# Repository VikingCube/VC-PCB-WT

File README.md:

# VikingCube WT PCB

Repository for VikingCube WT Boards

https://vikingcube.com

# Legal
You are free to download, build, modify VikingCube Midi with absolutely no fee and any kind of guarantee. We believe in the mindset of opensource - if you like please
mark the source with references for this repositroy or our website: www.vikingcube.com

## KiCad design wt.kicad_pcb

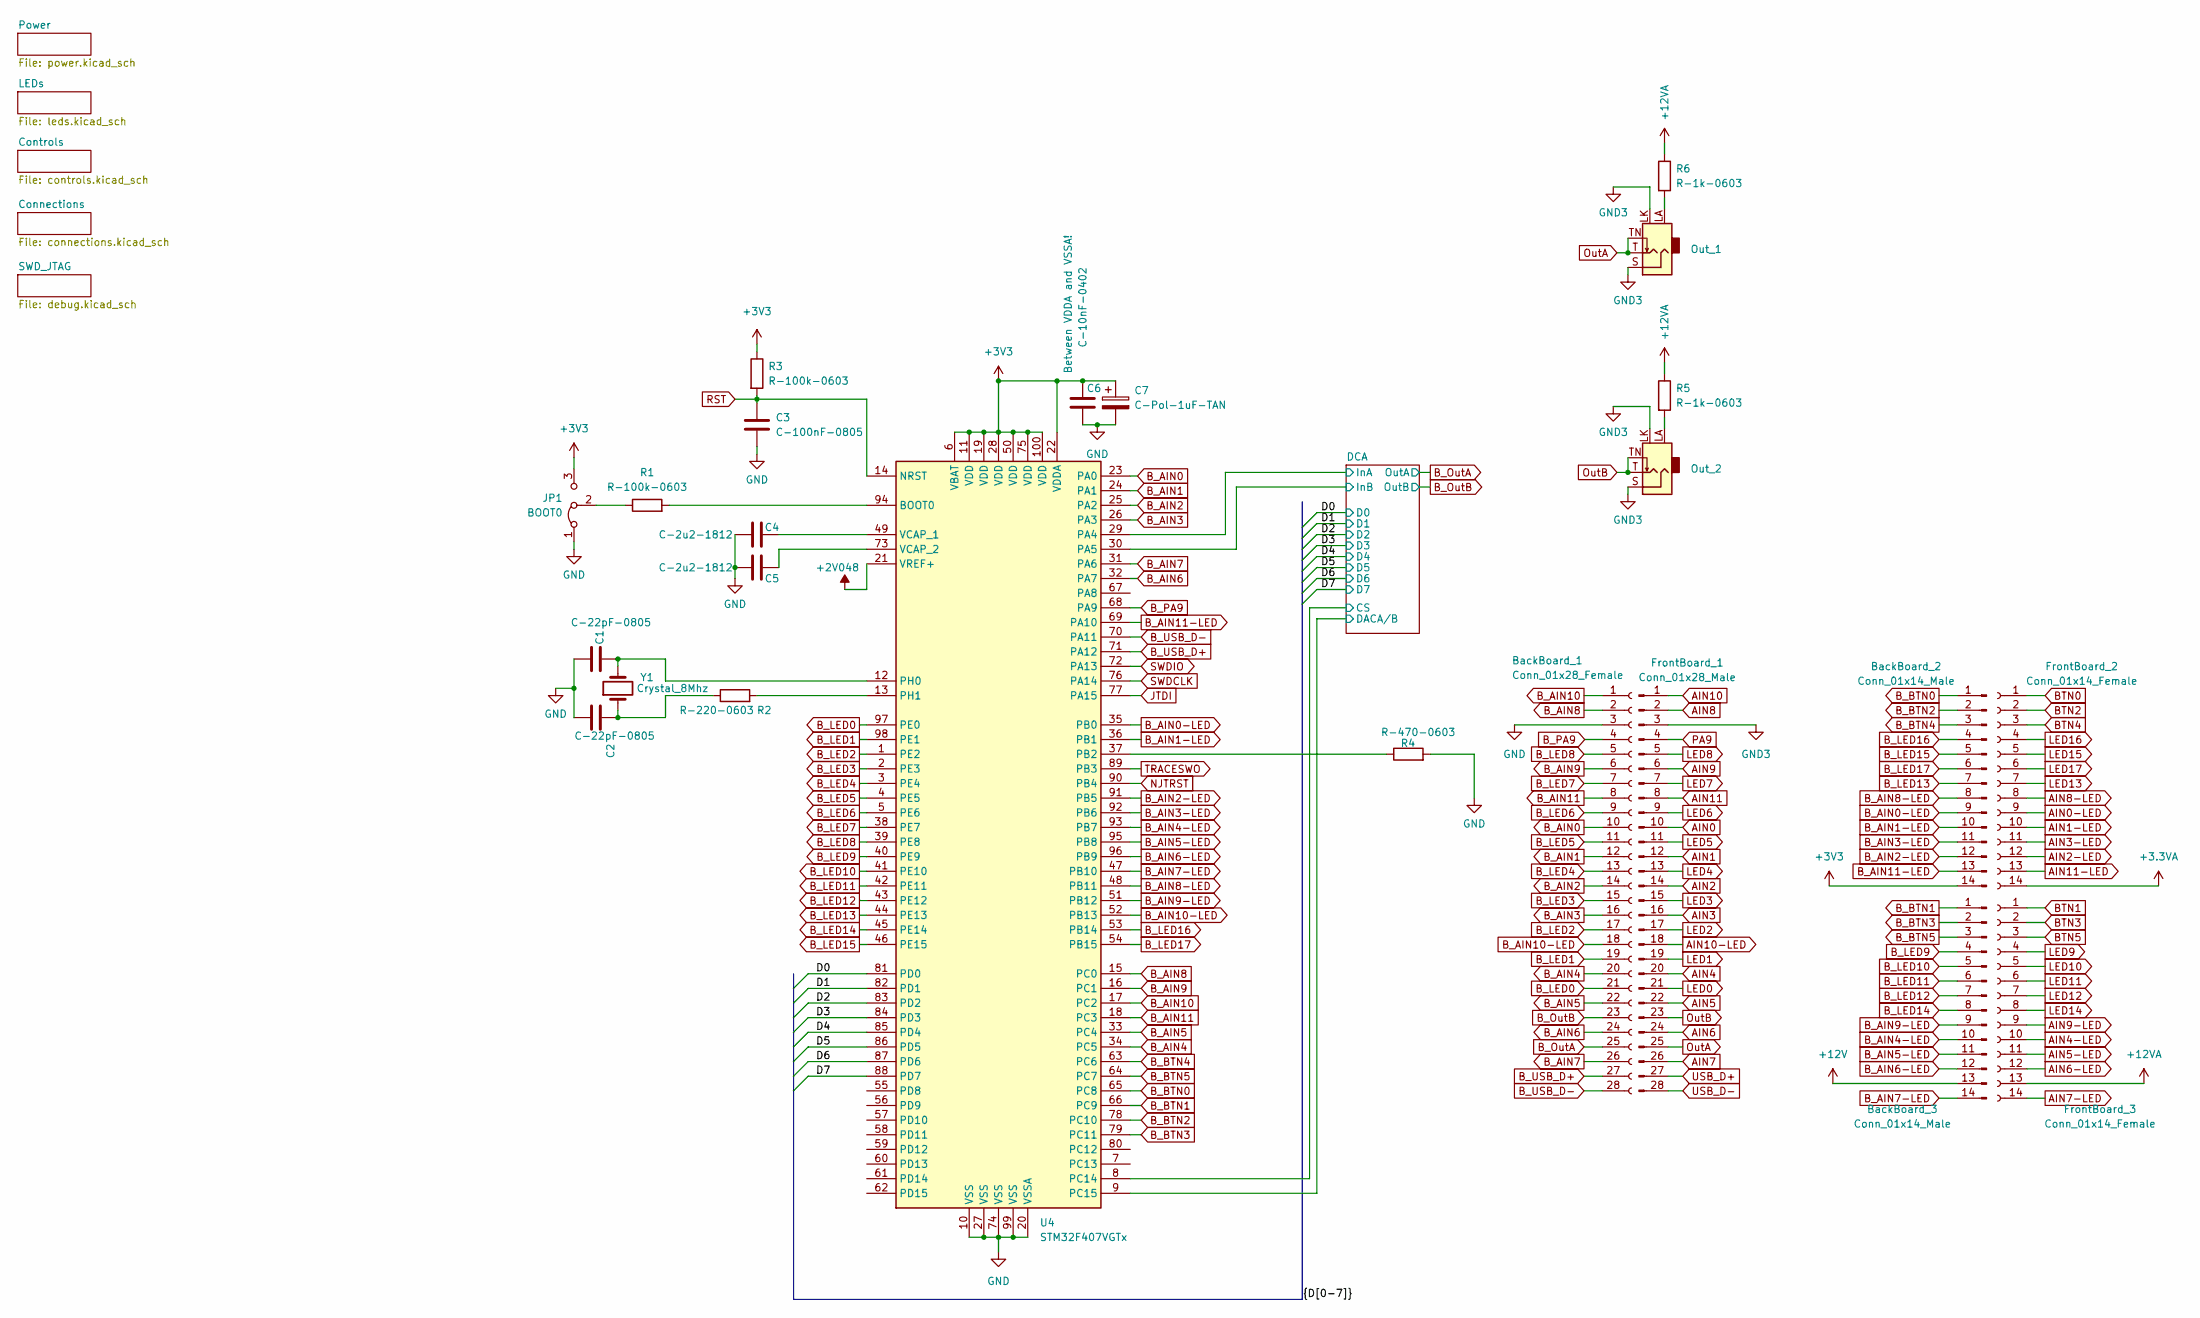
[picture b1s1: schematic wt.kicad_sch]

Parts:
BackBoard_1: Conn_01x28_Female; PinSocket_2x14_P2.54mm_Vertical
BackBoard_2, BackBoard_3: Conn_01x14_Male; PinHeader_1x14_P2.54mm_Vertical
C1, C2: C-22pF-0805; C_0805_2012Metric_Pad1.18x1.45mm_HandSolder; Tolerance 5%; Voltage 50V
C3: C-100nF-0805; C_0805_2012Metric_Pad1.18x1.45mm_HandSolder
C4, C5: C-2u2-1812; C_0603_1608Metric
C6: C-10nF-0402; C_0402_1005Metric
C7: C-Pol-1uF-TAN; CP_EIA-3216-18_Kemet-A
FrontBoard_1: Conn_01x28_Male; PinHeader_2x14_P2.54mm_Vertical
FrontBoard_2, FrontBoard_3: Conn_01x14_Female; PinSocket_1x14_P2.54mm_Vertical
JP1: BOOT0; PinHeader_1x03_P2.54mm_Vertical
Out_1, Out_2: LUM-1502-03_3.5mm_mono_vertical_jack; LUM 1502-03 LED
R1, R3: R-100k-0603; R_0603_1608Metric
R2: R-220-0603; R_0201_0603Metric_Pad0.64x0.40mm_HandSolder
R4: R-470-0603; R_0201_0603Metric_Pad0.64x0.40mm_HandSolder; Tolerance 5%
R5, R6: R-1k-0603; R_0603_1608Metric_Pad0.98x0.95mm_HandSolder; Tolerance 5%
U4: STM32F407VGTx; LQFP-100_14x14mm_P0.5mm
Y1: Crystal_8Mhz; HC49-4HSMX

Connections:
1V25: U4.21 (VREF+); also elsewhere on the board
+3.3VA: FrontBoard_2.14; also elsewhere on the board
+3V3: BackBoard_2.14, C6.1, C7.1, JP1.3 (B), R3.1, U4.6 (VBAT), U4.11 (VDD), U4.19 (VDD), U4.22 (VDDA), U4.28 (VDD), U4.50 (VDD), U4.75 (VDD), U4.100 (VDD); also elsewhere on the board
+12V: BackBoard_3.13; also elsewhere on the board
+12VA: FrontBoard_3.13, R5.1, R6.1; also elsewhere on the board
/D0: U4.81 (PD0); also elsewhere on the board
/D1: U4.82 (PD1); also elsewhere on the board
/D2: U4.83 (PD2); also elsewhere on the board
/D3: U4.84 (PD3); also elsewhere on the board
/D4: U4.85 (PD4); also elsewhere on the board
/D5: U4.86 (PD5); also elsewhere on the board
/D6: U4.87 (PD6); also elsewhere on the board
/D7: U4.88 (PD7); also elsewhere on the board
/DCA/CS: U4.8 (PC14); also elsewhere on the board
/DCA/DACA/B: U4.9 (PC15); also elsewhere on the board
/DCA/InA: U4.29 (PA4); also elsewhere on the board
/DCA/InB: U4.30 (PA5); also elsewhere on the board
AIN0: FrontBoard_1.10; also elsewhere on the board
AIN0-LED: FrontBoard_2.9; also elsewhere on the board
AIN1: FrontBoard_1.12; also elsewhere on the board
AIN1-LED: FrontBoard_2.10; also elsewhere on the board
AIN2: FrontBoard_1.14; also elsewhere on the board
AIN2-LED: FrontBoard_2.12; also elsewhere on the board
AIN3: FrontBoard_1.16; also elsewhere on the board
AIN3-LED: FrontBoard_2.11; also elsewhere on the board
AIN4: FrontBoard_1.20; also elsewhere on the board
AIN4-LED: FrontBoard_3.10; also elsewhere on the board
AIN5: FrontBoard_1.22; also elsewhere on the board
AIN5-LED: FrontBoard_3.11; also elsewhere on the board
AIN6: FrontBoard_1.24; also elsewhere on the board
AIN6-LED: FrontBoard_3.12; also elsewhere on the board
AIN7: FrontBoard_1.26; also elsewhere on the board
AIN7-LED: FrontBoard_3.14; also elsewhere on the board
AIN8: FrontBoard_1.2; also elsewhere on the board
AIN8-LED: FrontBoard_2.8; also elsewhere on the board
AIN9: FrontBoard_1.6; also elsewhere on the board
AIN9-LED: FrontBoard_3.9; also elsewhere on the board
AIN10: FrontBoard_1.1; also elsewhere on the board
AIN10-LED: FrontBoard_1.18; also elsewhere on the board
AIN11: FrontBoard_1.8; also elsewhere on the board
AIN11-LED: FrontBoard_2.13; also elsewhere on the board
BTN0: FrontBoard_2.1; also elsewhere on the board
BTN1: FrontBoard_3.1; also elsewhere on the board
BTN2: FrontBoard_2.2; also elsewhere on the board
BTN3: FrontBoard_3.2; also elsewhere on the board
BTN4: FrontBoard_2.3; also elsewhere on the board
BTN5: FrontBoard_3.3; also elsewhere on the board
B_AIN0: BackBoard_1.10, U4.23 (PA0)
B_AIN0-LED: BackBoard_2.9, U4.35 (PB0)
B_AIN1: BackBoard_1.12, U4.24 (PA1)
B_AIN1-LED: BackBoard_2.10, U4.36 (PB1)
B_AIN2: BackBoard_1.14, U4.25 (PA2)
B_AIN2-LED: BackBoard_2.12, U4.91 (PB5)
B_AIN3: BackBoard_1.16, U4.26 (PA3)
B_AIN3-LED: BackBoard_2.11, U4.92 (PB6)
B_AIN4: BackBoard_1.20, U4.34 (PC5)
B_AIN4-LED: BackBoard_3.10, U4.93 (PB7)
B_AIN5: BackBoard_1.22, U4.33 (PC4)
B_AIN5-LED: BackBoard_3.11, U4.95 (PB8)
B_AIN6: BackBoard_1.24, U4.32 (PA7)
B_AIN6-LED: BackBoard_3.12, U4.96 (PB9)
B_AIN7: BackBoard_1.26, U4.31 (PA6)
B_AIN7-LED: BackBoard_3.14, U4.47 (PB10)
B_AIN8: BackBoard_1.2, U4.15 (PC0)
B_AIN8-LED: BackBoard_2.8, U4.48 (PB11)
B_AIN9: BackBoard_1.6, U4.16 (PC1)
B_AIN9-LED: BackBoard_3.9, U4.51 (PB12)
B_AIN10: BackBoard_1.1, U4.17 (PC2)
B_AIN10-LED: BackBoard_1.18, U4.52 (PB13)
B_AIN11: BackBoard_1.8, U4.18 (PC3)
B_AIN11-LED: BackBoard_2.13, U4.69 (PA10)
B_BTN0: BackBoard_2.1, U4.65 (PC8)
B_BTN1: BackBoard_3.1, U4.66 (PC9)
B_BTN2: BackBoard_2.2, U4.78 (PC10)
B_BTN3: BackBoard_3.2, U4.79 (PC11)
B_BTN4: BackBoard_2.3, U4.63 (PC6)
B_BTN5: BackBoard_3.3, U4.64 (PC7)
B_LED0: BackBoard_1.21, U4.97 (PE0)
B_LED1: BackBoard_1.19, U4.98 (PE1)
B_LED2: BackBoard_1.17, U4.1 (PE2)
B_LED3: BackBoard_1.15, U4.2 (PE3)
B_LED4: BackBoard_1.13, U4.3 (PE4)
B_LED5: BackBoard_1.11, U4.4 (PE5)
B_LED6: BackBoard_1.9, U4.5 (PE6)
B_LED7: BackBoard_1.7, U4.38 (PE7)
B_LED8: BackBoard_1.5, U4.39 (PE8)
B_LED9: BackBoard_3.4, U4.40 (PE9)
B_LED10: BackBoard_3.5, U4.41 (PE10)
B_LED11: BackBoard_3.6, U4.42 (PE11)
B_LED12: BackBoard_3.7, U4.43 (PE12)
B_LED13: BackBoard_2.7, U4.44 (PE13)
B_LED14: BackBoard_3.8, U4.45 (PE14)
B_LED15: BackBoard_2.5, U4.46 (PE15)
B_LED16: BackBoard_2.4, U4.53 (PB14)
B_LED17: BackBoard_2.6, U4.54 (PB15)
B_OutA: BackBoard_1.25; also elsewhere on the board
B_OutB: BackBoard_1.23; also elsewhere on the board
B_PA9: BackBoard_1.4, U4.68 (PA9)
B_USB_D+: BackBoard_1.27, U4.71 (PA12)
B_USB_D-: BackBoard_1.28, U4.70 (PA11)
GND: BackBoard_1.3, C1.2, C2.2, C3.2, C4.2, C5.2, C6.2, C7.2, JP1.1 (A), R4.2, U4.10 (VSS), U4.20 (VSSA), U4.27 (VSS), U4.74 (VSS), U4.99 (VSS); also elsewhere on the board
GND3: FrontBoard_1.3, Out_1.LK, Out_1.S, Out_2.LK, Out_2.S; also elsewhere on the board
JTDI: U4.77 (PA15); also elsewhere on the board
LED0: FrontBoard_1.21; also elsewhere on the board
LED1: FrontBoard_1.19; also elsewhere on the board
LED2: FrontBoard_1.17; also elsewhere on the board
LED3: FrontBoard_1.15; also elsewhere on the board
LED4: FrontBoard_1.13; also elsewhere on the board
LED5: FrontBoard_1.11; also elsewhere on the board
LED6: FrontBoard_1.9; also elsewhere on the board
LED7: FrontBoard_1.7; also elsewhere on the board
LED8: FrontBoard_1.5; also elsewhere on the board
LED9: FrontBoard_3.4; also elsewhere on the board
LED10: FrontBoard_3.5; also elsewhere on the board
LED11: FrontBoard_3.6; also elsewhere on the board
LED12: FrontBoard_3.7; also elsewhere on the board
LED13: FrontBoard_2.7; also elsewhere on the board
LED14: FrontBoard_3.8; also elsewhere on the board
LED15: FrontBoard_2.5; also elsewhere on the board
LED16: FrontBoard_2.4; also elsewhere on the board
LED17: FrontBoard_2.6; also elsewhere on the board
NJTRST: U4.90 (PB4)
unnamed: C2.1, R2.1, Y1.1
unnamed: JP1.2 (C), R1.1
unnamed: Out_2.LA, R5.2
unnamed: R1.2, U4.94 (BOOT0)
unnamed: R4.1, U4.37 (PB2)
unnamed: C1.1, U4.12 (PH0), Y1.2
unnamed: R2.2, U4.13 (PH1)
unnamed: C4.1, U4.49 (VCAP_1)
unnamed: C5.1, U4.73 (VCAP_2)
OutA: FrontBoard_1.25, Out_1.T, Out_1.TN
OutB: FrontBoard_1.23, Out_2.T, Out_2.TN
PA9: FrontBoard_1.4; also elsewhere on the board
RST: C3.1, R3.2, U4.14 (NRST); also elsewhere on the board
SWDCLK: U4.76 (PA14); also elsewhere on the board
SWDIO: U4.72 (PA13); also elsewhere on the board
TRACESWO: U4.89 (PB3); also elsewhere on the board
USB_D+: FrontBoard_1.27; also elsewhere on the board
USB_D-: FrontBoard_1.28; also elsewhere on the board

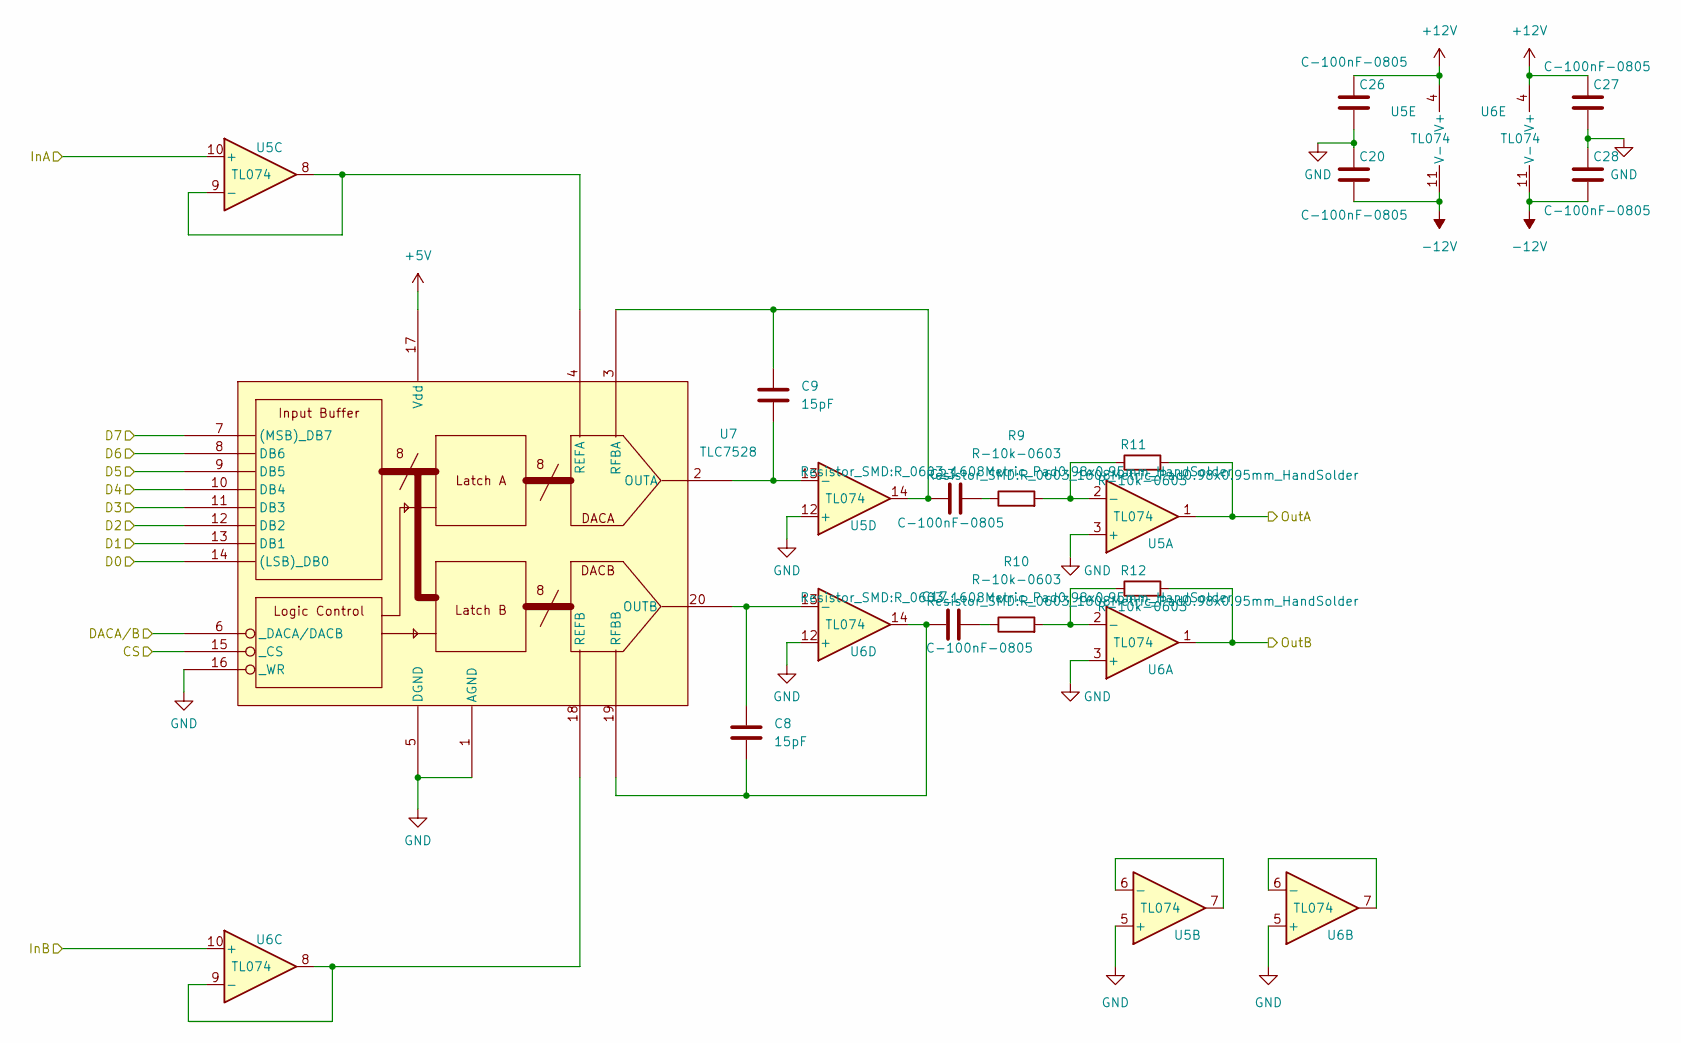
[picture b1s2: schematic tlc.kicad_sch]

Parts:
C8, C9: 15pF; C_1206_3216Metric_Pad1.33x1.80mm_HandSolder
C17, C20, C23, C26, C27, C28: C-100nF-0805; C_0805_2012Metric_Pad1.18x1.45mm_HandSolder
R9, R10, R11, R12: R-10k-0603; R_0603_1608Metric_Pad0.98x0.95mm_HandSolder
U5, U6: TL074; SO-14_5.3x10.2mm_P1.27mm
U7: TLC7528; SOIC-20W_7.5x12.8mm_P1.27mm

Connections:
+5V: U7.17 (Vdd); also elsewhere on the board
+12V: C26.1, C27.1, U5.4 (V+), U6.4 (V+); also elsewhere on the board
-12V: C20.2, C28.2, U5.11 (V-), U6.11 (V-); also elsewhere on the board
/D0: U7.14 ((LSB)_DB0); also elsewhere on the board
/D1: U7.13 (DB1); also elsewhere on the board
/D2: U7.12 (DB2); also elsewhere on the board
/D3: U7.11 (DB3); also elsewhere on the board
/D4: U7.10 (DB4); also elsewhere on the board
/D5: U7.9 (DB5); also elsewhere on the board
/D6: U7.8 (DB6); also elsewhere on the board
/D7: U7.7 ((MSB)_DB7); also elsewhere on the board
/DCA/CS: U7.15 (_CS); also elsewhere on the board
/DCA/DACA/B: U7.6 (_DACA/DACB); also elsewhere on the board
/DCA/InA: U5.10 (+); also elsewhere on the board
/DCA/InB: U6.10 (+); also elsewhere on the board
B_OutA: R11.2, U5.1; also elsewhere on the board
B_OutB: R12.2, U6.1; also elsewhere on the board
GND: C20.1, C26.2, C27.2, C28.1, U5.3 (+), U5.5 (+), U5.12 (+), U6.3 (+), U6.5 (+), U6.12 (+), U7.1 (AGND), U7.5 (DGND), U7.16 (_WR); also elsewhere on the board
unnamed: C17.2, R10.1
unnamed: C23.2, R9.1
unnamed: R9.2, R11.1, U5.2 (-)
unnamed: U5.6 (-), U5.7
unnamed: U5.8, U5.9 (-), U7.4 (REFA)
unnamed: C9.2, U5.13 (-), U7.2 (OUTA)
unnamed: R10.2, R12.1, U6.2 (-)
unnamed: U6.6 (-), U6.7
unnamed: U6.8, U6.9 (-), U7.18 (REFB)
unnamed: C8.1, U6.13 (-), U7.20 (OUTB)
unnamed: C9.1, C23.1, U5.14, U7.3 (RFBA)
unnamed: C8.2, C17.1, U6.14, U7.19 (RFBB)

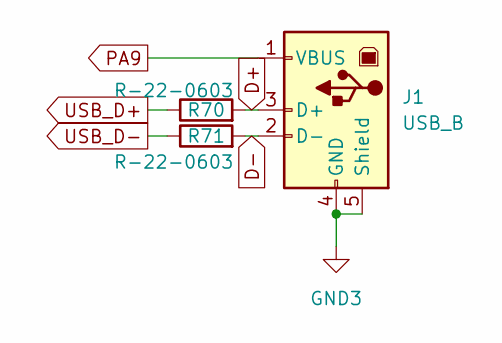
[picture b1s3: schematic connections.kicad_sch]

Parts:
J1: USB_B; USB-BG
R70, R71: R-22-0603; R_0201_0603Metric_Pad0.64x0.40mm_HandSolder

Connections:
D+: J1.3 (D+), R70.2
D-: J1.2 (D-), R71.2
GND3: J1.4 (GND), J1.5 (Shield); also elsewhere on the board
PA9: J1.1 (VBUS); also elsewhere on the board
USB_D+: R70.1; also elsewhere on the board
USB_D-: R71.1; also elsewhere on the board

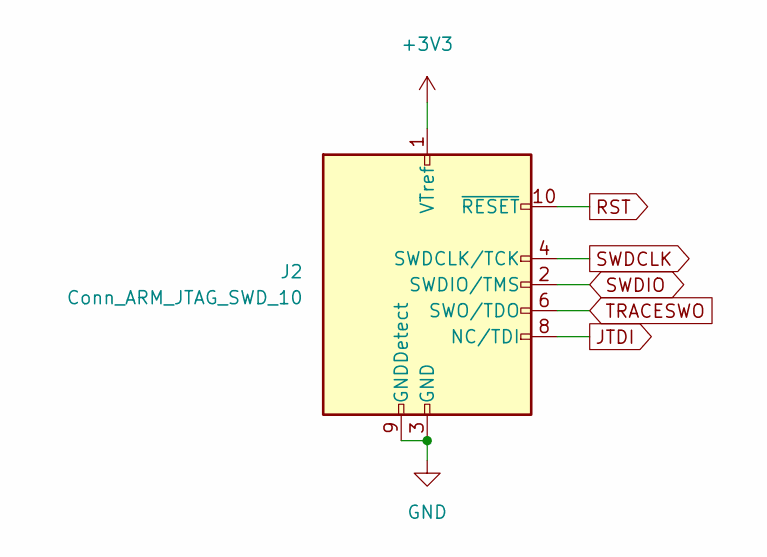
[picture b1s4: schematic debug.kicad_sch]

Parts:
J2: Conn_ARM_JTAG_SWD_10; PinHeader_2x05_P2.54mm_Vertical

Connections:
+3V3: J2.1 (VTref); also elsewhere on the board
GND: J2.3 (GND), J2.5 (GND), J2.9 (GNDDetect); also elsewhere on the board
JTDI: J2.8 (NC/TDI); also elsewhere on the board
RST: J2.10 (~RESET); also elsewhere on the board
SWDCLK: J2.4 (SWDCLK/TCK); also elsewhere on the board
SWDIO: J2.2 (SWDIO/TMS); also elsewhere on the board
TRACESWO: J2.6 (SWO/TDO); also elsewhere on the board

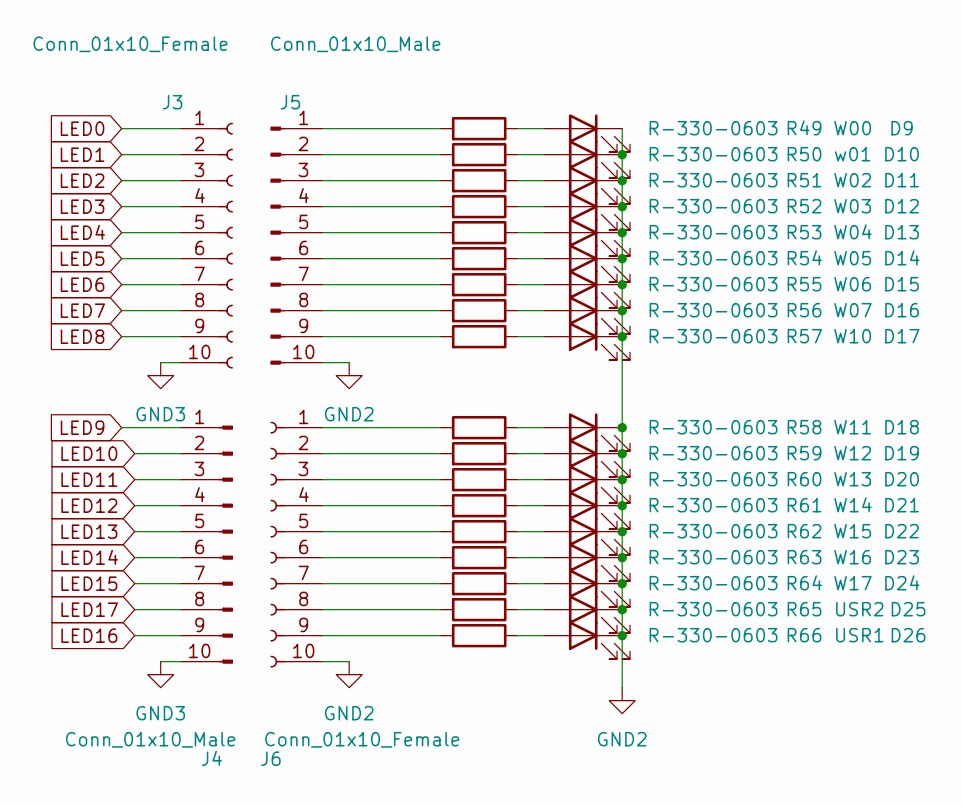
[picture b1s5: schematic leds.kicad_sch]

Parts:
D9: W00; D_1206_3216Metric_Pad1.42x1.75mm_HandSolder
D10: w01; D_1206_3216Metric_Pad1.42x1.75mm_HandSolder
D11: W02; D_1206_3216Metric_Pad1.42x1.75mm_HandSolder
D12: W03; D_1206_3216Metric_Pad1.42x1.75mm_HandSolder
D13: W04; D_1206_3216Metric_Pad1.42x1.75mm_HandSolder
D14: W05; D_1206_3216Metric_Pad1.42x1.75mm_HandSolder
D15: W06; D_1206_3216Metric_Pad1.42x1.75mm_HandSolder
D16: W07; D_1206_3216Metric_Pad1.42x1.75mm_HandSolder
D17: W10; D_1206_3216Metric_Pad1.42x1.75mm_HandSolder
D18: W11; D_1206_3216Metric_Pad1.42x1.75mm_HandSolder
D19: W12; D_1206_3216Metric_Pad1.42x1.75mm_HandSolder
D20: W13; D_1206_3216Metric_Pad1.42x1.75mm_HandSolder
D21: W14; D_1206_3216Metric_Pad1.42x1.75mm_HandSolder
D22: W15; D_1206_3216Metric_Pad1.42x1.75mm_HandSolder
D23: W16; D_1206_3216Metric_Pad1.42x1.75mm_HandSolder
D24: W17; D_1206_3216Metric_Pad1.42x1.75mm_HandSolder
D25: USR2; D_1206_3216Metric_Pad1.42x1.75mm_HandSolder
D26: USR1; D_1206_3216Metric_Pad1.42x1.75mm_HandSolder
J3: Conn_01x10_Female; PinHeader_1x10_P2.54mm_Vertical
J4: Conn_01x10_Male; PinHeader_2x05_P2.54mm_Vertical
J5: Conn_01x10_Male; PinSocket_1x10_P2.54mm_Vertical
J6: Conn_01x10_Female; PinSocket_2x05_P2.54mm_Vertical
R49, R50, R51, R52, R53, R54, R55, R56, R57, R58, R59, R60, R61, R62, R63, R64, R65, R66: R-330-0603; R_0603_1608Metric_Pad0.98x0.95mm_HandSolder; Tolerance 5%

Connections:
GND2: D9.1 (K), D10.1 (K), D11.1 (K), D12.1 (K), D13.1 (K), D14.1 (K), D15.1 (K), D16.1 (K), D17.1 (K), D18.1 (K), D19.1 (K), D20.1 (K), D21.1 (K), D22.1 (K), D23.1 (K), D24.1 (K), D25.1 (K), D26.1 (K), J5.10, J6.10
GND3: J3.10, J4.10; also elsewhere on the board
LED0: J3.1; also elsewhere on the board
LED1: J3.2; also elsewhere on the board
LED2: J3.3; also elsewhere on the board
LED3: J3.4; also elsewhere on the board
LED4: J3.5; also elsewhere on the board
LED5: J3.6; also elsewhere on the board
LED6: J3.7; also elsewhere on the board
LED7: J3.8; also elsewhere on the board
LED8: J3.9; also elsewhere on the board
LED9: J4.1; also elsewhere on the board
LED10: J4.2; also elsewhere on the board
LED11: J4.3; also elsewhere on the board
LED12: J4.4; also elsewhere on the board
LED13: J4.5; also elsewhere on the board
LED14: J4.6; also elsewhere on the board
LED15: J4.7; also elsewhere on the board
LED16: J4.9; also elsewhere on the board
LED17: J4.8; also elsewhere on the board
unnamed: D9.2 (A), R49.1
unnamed: D10.2 (A), R50.1
unnamed: D11.2 (A), R51.1
unnamed: D12.2 (A), R52.1
unnamed: D13.2 (A), R53.1
unnamed: D14.2 (A), R54.1
unnamed: D15.2 (A), R55.1
unnamed: D16.2 (A), R56.1
unnamed: D17.2 (A), R57.1
unnamed: D18.2 (A), R58.1
unnamed: D19.2 (A), R59.1
unnamed: D20.2 (A), R60.1
unnamed: D21.2 (A), R61.1
unnamed: D22.2 (A), R62.1
unnamed: D23.2 (A), R63.1
unnamed: D24.2 (A), R64.1
unnamed: D25.2 (A), R65.1
unnamed: D26.2 (A), R66.1
unnamed: J5.1, R49.2
unnamed: J5.2, R50.2
unnamed: J5.3, R51.2
unnamed: J5.4, R52.2
unnamed: J5.5, R53.2
unnamed: J5.6, R54.2
unnamed: J5.7, R55.2
unnamed: J5.8, R56.2
unnamed: J5.9, R57.2
unnamed: J6.1, R58.2
unnamed: J6.2, R59.2
unnamed: J6.3, R60.2
unnamed: J6.4, R61.2
unnamed: J6.5, R62.2
unnamed: J6.6, R63.2
unnamed: J6.7, R64.2
unnamed: J6.8, R65.2
unnamed: J6.9, R66.2

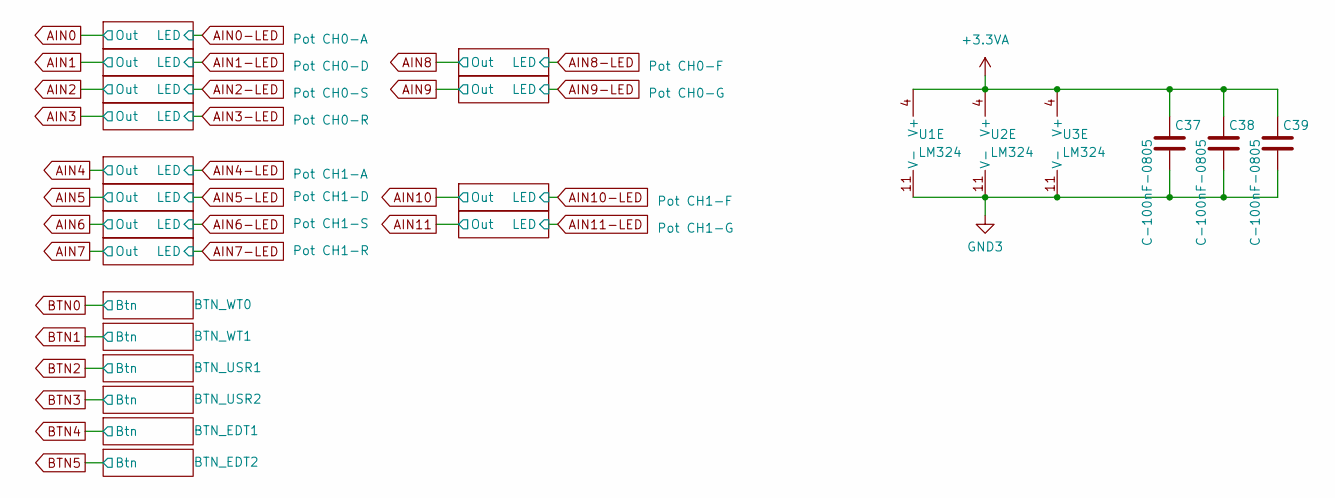
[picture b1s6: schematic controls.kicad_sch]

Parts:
C37, C38, C39: C-100nF-0805; C_0805_2012Metric_Pad1.18x1.45mm_HandSolder
U1, U2, U3: LM324; SO-14_3.9x8.65mm_P1.27mm

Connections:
+3.3VA: C37.1, C38.1, C39.1, U1.4 (V+), U2.4 (V+), U3.4 (V+); also elsewhere on the board
GND3: C37.2, C38.2, C39.2, U1.11 (V-), U2.11 (V-), U3.11 (V-); also elsewhere on the board
unnamed 248: U1.5 (+); also elsewhere on the board
unnamed 249: U1.6 (-), U1.7; also elsewhere on the board
unnamed 250: U1.10 (+); also elsewhere on the board
unnamed 251: U1.8, U1.9 (-); also elsewhere on the board
unnamed 252: U1.12 (+); also elsewhere on the board
unnamed 253: U1.13 (-), U1.14; also elsewhere on the board
unnamed 256: U2.5 (+); also elsewhere on the board
unnamed 257: U2.6 (-), U2.7; also elsewhere on the board
unnamed 258: U2.10 (+); also elsewhere on the board
unnamed 259: U2.8, U2.9 (-); also elsewhere on the board
unnamed 260: U2.12 (+); also elsewhere on the board
unnamed 261: U2.13 (-), U2.14; also elsewhere on the board
unnamed 264: U3.5 (+); also elsewhere on the board
unnamed 265: U3.6 (-), U3.7; also elsewhere on the board
unnamed 266: U3.10 (+); also elsewhere on the board
unnamed 267: U3.8, U3.9 (-); also elsewhere on the board
unnamed 268: U3.12 (+); also elsewhere on the board
unnamed 269: U3.13 (-), U3.14; also elsewhere on the board

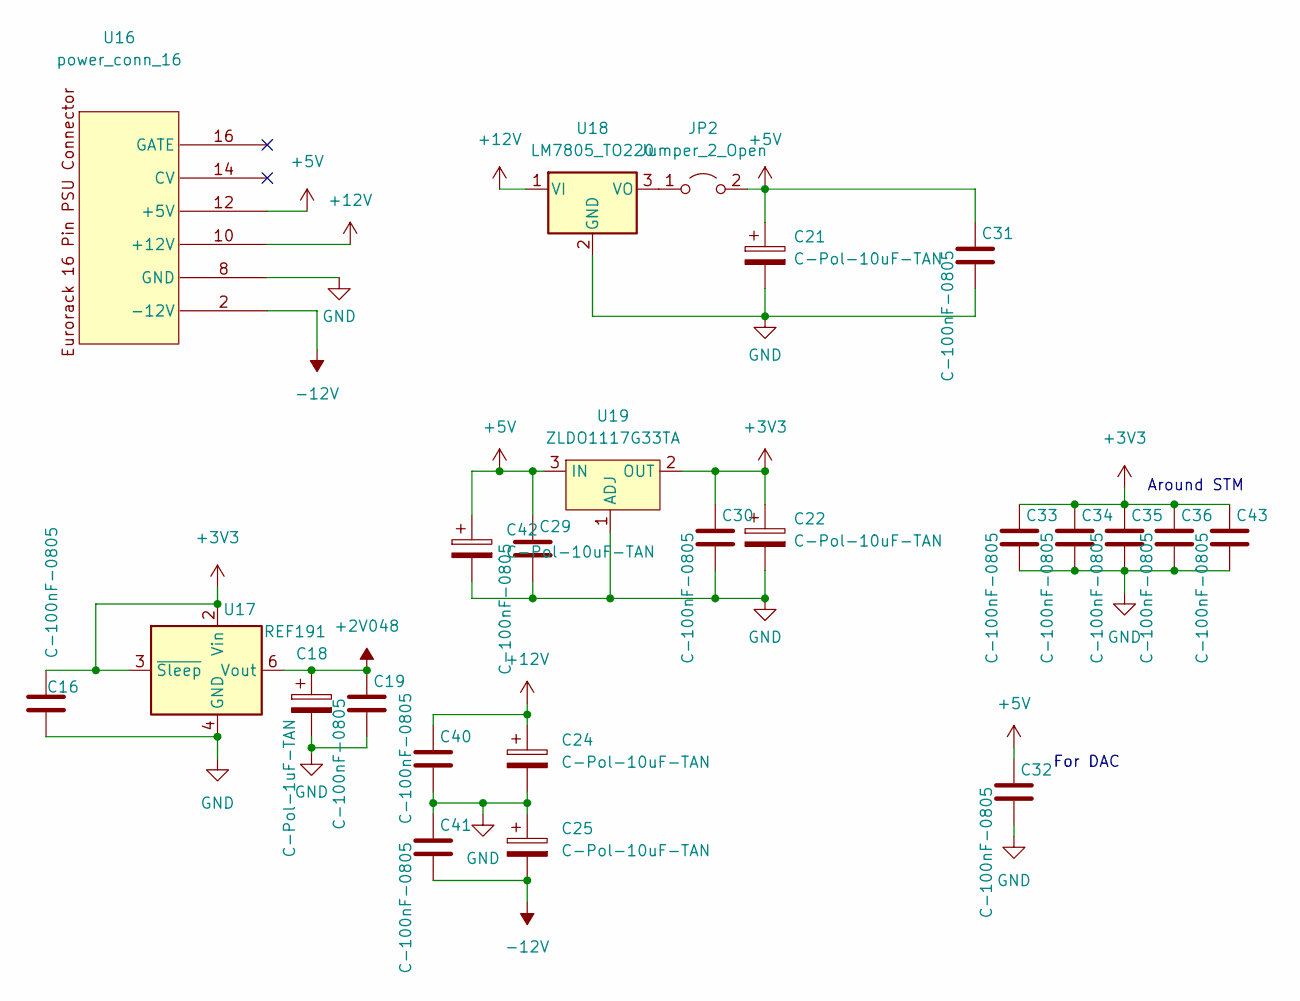
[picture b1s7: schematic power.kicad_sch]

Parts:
C16, C19, C29, C30, C31, C32, C33, C34, C35, C36, C40, C41, C43: C-100nF-0805; C_0805_2012Metric_Pad1.18x1.45mm_HandSolder
C18: C-Pol-1uF-TAN; CP_EIA-3216-18_Kemet-A
C21, C22, C24, C25, C42: C-Pol-10uF-TAN; CP_EIA-6032-28_Kemet-C
JP2: Jumper_2_Open; SolderJumper-2_P1.3mm_Open_Pad1.0x1.5mm
U16: power_conn_16; power_16
U17: REF191; SO-8_3.9x4.9mm_P1.27mm
U18: LM7805_TO220; TO-220-3_Vertical
U19: ZLDO1117G33TA; SOT-223

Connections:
1V25: C18.1, C19.1, U17.6 (Vout); also elsewhere on the board
+3V3: C16.1, C22.1, C30.1, C33.1, C34.1, C35.1, C36.1, C43.1, U17.2 (Vin), U17.3 (~Sleep), U19.2 (OUT), U19.4 (OUT); also elsewhere on the board
+5V: C21.1, C29.1, C31.1, C32.1, C42.1, JP2.2 (B), U16.11 (+5V), U16.12 (+5V), U19.3 (IN); also elsewhere on the board
+12V: C24.1, C40.1, U16.9 (+12V), U16.10 (+12V), U18.1 (VI); also elsewhere on the board
-12V: C25.2, C41.2, U16.1 (-12V), U16.2 (-12V); also elsewhere on the board
GND: C16.2, C18.2, C19.2, C21.2, C22.2, C24.2, C25.1, C29.2, C30.2, C31.2, C32.2, C33.2, C34.2, C35.2, C36.2, C40.2, C41.1, C42.2, C43.2, U16.3 (GND), U16.4 (GND), U16.5 (GND), U16.6 (GND), U16.7 (GND), U16.8 (GND), U17.4 (GND), U18.2 (GND), U19.1 (ADJ); also elsewhere on the board
unnamed: JP2.1 (A), U18.3 (VO)

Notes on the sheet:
Around STM
For DAC

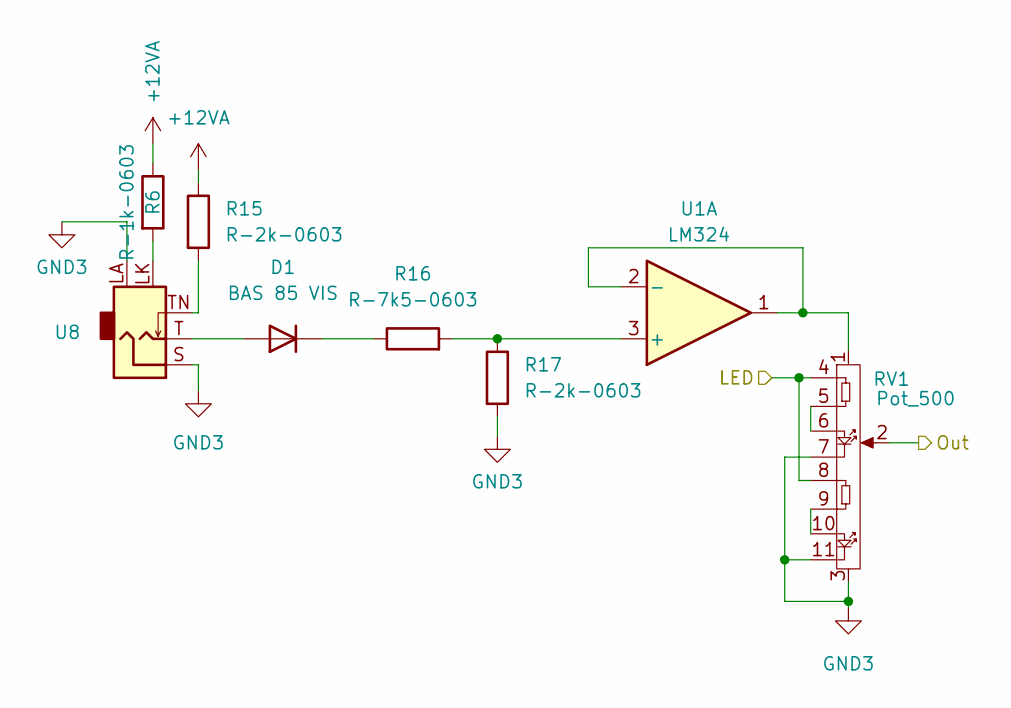
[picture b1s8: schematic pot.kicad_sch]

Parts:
D1: BAS 85 VIS; D_MiniMELF
R6: R-1k-0603; R_0603_1608Metric_Pad0.98x0.95mm_HandSolder; Tolerance 5%
R15, R17: R-2k-0603; R_0603_1608Metric_Pad0.98x0.95mm_HandSolder; Tolerance 1%
R16: R-7k5-0603; R_0603_1608Metric_Pad0.98x0.95mm_HandSolder; Tolerance 1%
RV1: Pot_500; Potentiometer_Piher_PT-10-V10_Vertical
U1: LM324; SO-14_3.9x8.65mm_P1.27mm
U8: LUM-1502-03_3.5mm_mono_vertical_jack; LUM 1502-03 LED

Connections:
+12VA: R6.1, R15.1; also elsewhere on the board
AIN0: RV1.2; also elsewhere on the board
AIN0-LED: RV1.4 (R), RV1.8 (R); also elsewhere on the board
GND3: R17.2, RV1.3, RV1.7 (LED-), RV1.11 (LED-), U8.LA, U8.S; also elsewhere on the board
unnamed: D1.1 (A), U8.T
unnamed: D1.2 (K), R16.1
unnamed: R15.2, U8.TN
unnamed: RV1.5 (R), RV1.6 (LED+)
unnamed: RV1.9 (R), RV1.10 (LED+)
unnamed: R16.2, R17.1, U1.3 (+)
unnamed: RV1.1, U1.1, U1.2 (-)
unnamed 248: U1.5 (+); also elsewhere on the board
unnamed 249: U1.6 (-), U1.7; also elsewhere on the board
unnamed 250: U1.10 (+); also elsewhere on the board
unnamed 251: U1.8, U1.9 (-); also elsewhere on the board
unnamed 252: U1.12 (+); also elsewhere on the board
unnamed 253: U1.13 (-), U1.14; also elsewhere on the board

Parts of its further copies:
D2, D3, D4, D5, D6, D7, D8, D27, D28, D29, D30: BAS 85 VIS; D_MiniMELF
R7, R8, R81, R82, R83, R84, R85, R86, R87, R88, R89, R90: R-1k-0603; R_0603_1608Metric_Pad0.98x0.95mm_HandSolder; Tolerance 5%
R18, R20, R21, R23, R24, R26, R27, R29, R32, R34, R35, R37, R46, R48, R67, R69, R72, R74, R75, R77, R78, R80: R-2k-0603; R_0603_1608Metric_Pad0.98x0.95mm_HandSolder; Tolerance 1%
R19, R22, R25, R28, R33, R36, R47, R68, R73, R76, R79: R-7k5-0603; R_0603_1608Metric_Pad0.98x0.95mm_HandSolder; Tolerance 1%
RV2, RV3, RV4, RV5, RV6, RV7, RV8, RV10, RV11, RV12, RV13: Pot_500; Potentiometer_Piher_PT-10-V10_Vertical
U9, U10, U11, U12, U13, U14, U15, U21, U22, U23, U24: LUM-1502-03_3.5mm_mono_vertical_jack; LUM 1502-03 LED

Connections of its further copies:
+12VA: R7.1, R8.1, R18.1, R21.1, R24.1, R27.1, R32.1, R35.1, R46.1, R67.1, R72.1, R75.1, R78.1, R81.1, R82.1, R83.1, R84.1, R85.1, R86.1, R87.1, R88.1, R89.1, R90.1; also elsewhere on the board
AIN1: RV2.2; also elsewhere on the board
AIN1-LED: RV2.4 (R), RV2.8 (R); also elsewhere on the board
AIN2: RV3.2; also elsewhere on the board
AIN2-LED: RV3.4 (R), RV3.8 (R); also elsewhere on the board
AIN3: RV4.2; also elsewhere on the board
AIN3-LED: RV4.4 (R), RV4.8 (R); also elsewhere on the board
AIN4: RV5.2; also elsewhere on the board
AIN4-LED: RV5.4 (R), RV5.8 (R); also elsewhere on the board
AIN5: RV10.2; also elsewhere on the board
AIN5-LED: RV10.4 (R), RV10.8 (R); also elsewhere on the board
AIN6: RV6.2; also elsewhere on the board
AIN6-LED: RV6.4 (R), RV6.8 (R); also elsewhere on the board
AIN7: RV7.2; also elsewhere on the board
AIN7-LED: RV7.4 (R), RV7.8 (R); also elsewhere on the board
AIN8: RV8.2; also elsewhere on the board
AIN8-LED: RV8.4 (R), RV8.8 (R); also elsewhere on the board
AIN9: RV11.2; also elsewhere on the board
AIN9-LED: RV11.4 (R), RV11.8 (R); also elsewhere on the board
AIN10: RV12.2; also elsewhere on the board
AIN10-LED: RV12.4 (R), RV12.8 (R); also elsewhere on the board
AIN11: RV13.2; also elsewhere on the board
AIN11-LED: RV13.4 (R), RV13.8 (R); also elsewhere on the board
GND3: R20.2, R23.2, R26.2, R29.2, R34.2, R37.2, R48.2, R69.2, R74.2, R77.2, R80.2, RV2.3, RV2.7 (LED-), RV2.11 (LED-), RV3.3, RV3.7 (LED-), RV3.11 (LED-), RV4.3, RV4.7 (LED-), RV4.11 (LED-), RV5.3, RV5.7 (LED-), RV5.11 (LED-), RV6.3, RV6.7 (LED-), RV6.11 (LED-), RV7.3, RV7.7 (LED-), RV7.11 (LED-), RV8.3, RV8.7 (LED-), RV8.11 (LED-), RV10.3, RV10.7 (LED-), RV10.11 (LED-), RV11.3, RV11.7 (LED-), RV11.11 (LED-), RV12.3, RV12.7 (LED-), RV12.11 (LED-), RV13.3, RV13.7 (LED-), RV13.11 (LED-), U9.LA, U9.S, U10.LA, U10.S, U11.LA, U11.S, U12.LA, U12.S, U13.LA, U13.S, U14.LA, U14.S, U15.LA, U15.S, U21.LA, U21.S, U22.LA, U22.S, U23.LA, U23.S, U24.LA, U24.S; also elsewhere on the board
unnamed: D2.1 (A), U9.T
unnamed: D2.2 (K), R19.1
unnamed: D3.1 (A), U10.T
unnamed: D3.2 (K), R22.1
unnamed: D4.1 (A), U11.T
unnamed: D4.2 (K), R25.1
unnamed: D5.1 (A), U12.T
unnamed: D5.2 (K), R28.1
unnamed: D6.1 (A), U13.T
unnamed: D6.2 (K), R33.1
unnamed: D7.1 (A), U14.T
unnamed: D7.2 (K), R36.1
unnamed: D8.1 (A), U15.T
unnamed: D8.2 (K), R47.1
unnamed: D27.1 (A), U21.T
unnamed: D27.2 (K), R68.1
unnamed: D28.1 (A), U22.T
unnamed: D28.2 (K), R73.1
unnamed: D29.1 (A), U23.T
unnamed: D29.2 (K), R76.1
unnamed: D30.1 (A), U24.T
unnamed: D30.2 (K), R79.1
unnamed: R8.2, U9.LK
unnamed: R18.2, U9.TN
unnamed: R21.2, U10.TN
unnamed: R24.2, U11.TN
unnamed: R27.2, U12.TN
unnamed: R32.2, U13.TN
unnamed: R35.2, U14.TN
unnamed: R46.2, U15.TN
unnamed: R67.2, U21.TN
unnamed: R72.2, U22.TN
unnamed: R75.2, U23.TN
unnamed: R78.2, U24.TN
unnamed: R81.2, U10.LK
unnamed: R82.2, U11.LK
unnamed: R83.2, U12.LK
unnamed: R84.2, U13.LK
unnamed: R85.2, U14.LK
unnamed: R86.2, U15.LK
unnamed: R87.2, U21.LK
unnamed: R88.2, U22.LK
unnamed: R89.2, U23.LK
unnamed: R90.2, U24.LK
unnamed: RV2.5 (R), RV2.6 (LED+)
unnamed: RV2.9 (R), RV2.10 (LED+)
unnamed: RV3.5 (R), RV3.6 (LED+)
unnamed: RV3.9 (R), RV3.10 (LED+)
unnamed: RV4.5 (R), RV4.6 (LED+)
unnamed: RV4.9 (R), RV4.10 (LED+)
unnamed: RV5.5 (R), RV5.6 (LED+)
unnamed: RV5.9 (R), RV5.10 (LED+)
unnamed: RV6.5 (R), RV6.6 (LED+)
unnamed: RV6.9 (R), RV6.10 (LED+)
unnamed: RV7.5 (R), RV7.6 (LED+)
unnamed: RV7.9 (R), RV7.10 (LED+)
unnamed: RV8.5 (R), RV8.6 (LED+)
unnamed: RV8.9 (R), RV8.10 (LED+)
unnamed: RV10.5 (R), RV10.6 (LED+)
unnamed: RV10.9 (R), RV10.10 (LED+)
unnamed: RV11.5 (R), RV11.6 (LED+)
unnamed: RV11.9 (R), RV11.10 (LED+)
unnamed: RV12.5 (R), RV12.6 (LED+)
unnamed: RV12.9 (R), RV12.10 (LED+)
unnamed: RV13.5 (R), RV13.6 (LED+)
unnamed: RV13.9 (R), RV13.10 (LED+)
unnamed 248: R19.2, R20.1; also elsewhere on the board
unnamed 249: RV2.1; also elsewhere on the board
unnamed 250: R22.2, R23.1; also elsewhere on the board
unnamed 251: RV3.1; also elsewhere on the board
unnamed 252: R25.2, R26.1; also elsewhere on the board
unnamed 253: RV4.1; also elsewhere on the board
unnamed 254: R28.2, R29.1; also elsewhere on the board
unnamed 255: RV5.1; also elsewhere on the board
unnamed 256: R68.2, R69.1; also elsewhere on the board
unnamed 257: RV10.1; also elsewhere on the board
unnamed 258: R33.2, R34.1; also elsewhere on the board
unnamed 259: RV6.1; also elsewhere on the board
unnamed 260: R36.2, R37.1; also elsewhere on the board
unnamed 261: RV7.1; also elsewhere on the board
unnamed 262: R47.2, R48.1; also elsewhere on the board
unnamed 263: RV8.1; also elsewhere on the board
unnamed 264: R73.2, R74.1; also elsewhere on the board
unnamed 265: RV11.1; also elsewhere on the board
unnamed 266: R76.2, R77.1; also elsewhere on the board
unnamed 267: RV12.1; also elsewhere on the board
unnamed 268: R79.2, R80.1; also elsewhere on the board
unnamed 269: RV13.1; also elsewhere on the board
